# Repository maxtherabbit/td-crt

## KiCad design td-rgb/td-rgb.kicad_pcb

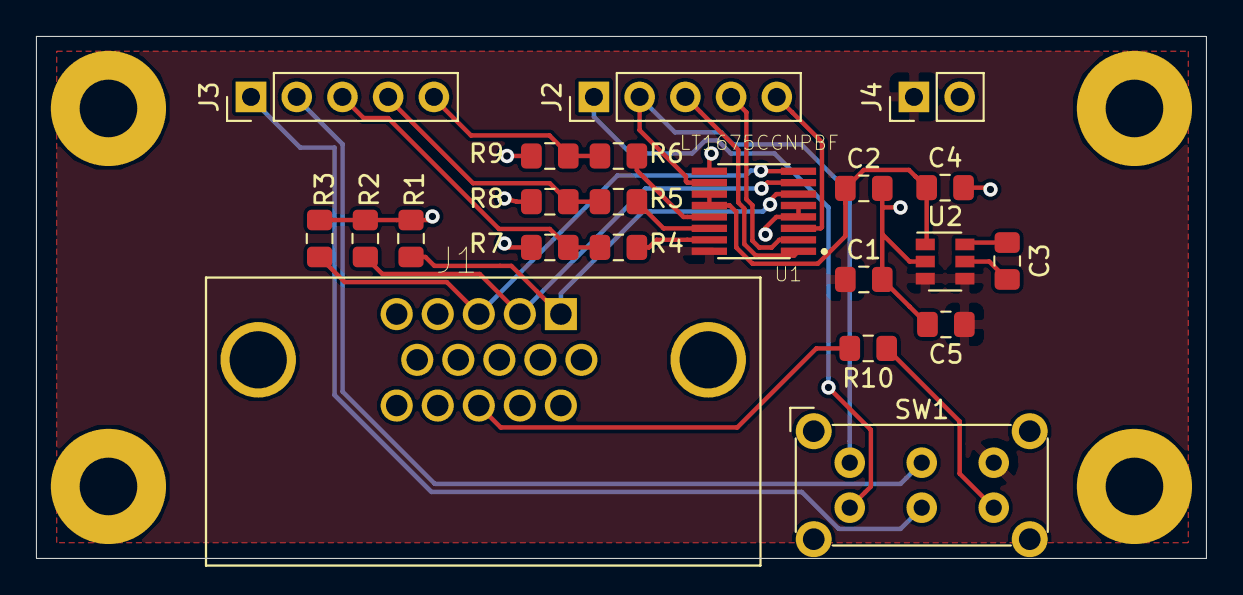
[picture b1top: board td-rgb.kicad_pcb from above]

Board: 2 copper layers, 65.0 x 29.0 mm, 22 parts (0 on the bottom side), 23 nets.

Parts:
C1, C2: 0.1uF; C_0805_2012Metric_Pad1.15x1.40mm_HandSolder
C3: 1uF; C_0805_2012Metric_Pad1.15x1.40mm_HandSolder
C4, C5: 2.2uF; C_0805_2012Metric_Pad1.15x1.40mm_HandSolder
J1: ICD15S13E4GV00LF; TE_1-1734530-1
J2, J3: Conn_01x05_Male; PinHeader_1x05_P2.54mm_Vertical
J4: Conn_01x02_Male; PinHeader_1x02_P2.54mm_Vertical
R1, R2, R3, R4, R5, R6, R7, R8, R9: 75; R_0805_2012Metric_Pad1.15x1.40mm_HandSolder
R10: 470; R_0805_2012Metric_Pad1.15x1.40mm_HandSolder
SW1: SW_DPDT_x2; SW_E-Switch_EG2219_DPDT_Angled
U1: LT1675CGNPBF; SOP63P600X172-16N
U2: LM2776; SOT-23-6

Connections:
+5V: C1.1, C5.1, J4.1, SW1.3, U1.16, U2.3, U2.4
-5V: C2.1, C4.1, U1.11, U1.12, U2.1
/blank_in: J2.2, SW1.1, U1.10
/blue: J1.3, R3.1, U1.8
/blue_in: J2.5, U1.3
/blue_out: J3.5, R6.1, R9.1
/csync_out: J3.1, SW1.5
/green: J1.2, R2.1, U1.7
/green_in: J2.4, U1.2
/green_out: J3.4, R5.1, R8.1
/red: J1.1, R1.1, U1.6
/red_in: J2.3, U1.1
/red_out: J3.3, R4.1, R7.1
GND: C1.2, C2.2, C4.2, C5.2, J1.5, J1.6, J1.7, J1.8, J1.10, J4.2, R1.2, R2.2, R3.2, R7.2, R8.2, R9.2, U1.4, U1.5, U1.9, U2.2
unnamed: C3.1, U2.5
unnamed: C3.2, U2.6
unnamed: J1.13, R10.2
unnamed: J2.1, SW1.4
unnamed: J3.2, SW1.2
unnamed: R4.2, U1.15
unnamed: R5.2, U1.14
unnamed: R6.2, U1.13
unnamed: R10.1, SW1.6

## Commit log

2019-02-11 Reverse pin numbering of output header to match input header, connect VGA pin 10 to ground
2019-02-11 Add series resistor to sync line from VGA (creating voltage divider when terminated into 75ohm at TV's composite video entry point) to attenuate TTL sync signals to video level

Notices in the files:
td-rgb/td-rgb.kicad_pcb:
td-rgb v1.0 CC0
